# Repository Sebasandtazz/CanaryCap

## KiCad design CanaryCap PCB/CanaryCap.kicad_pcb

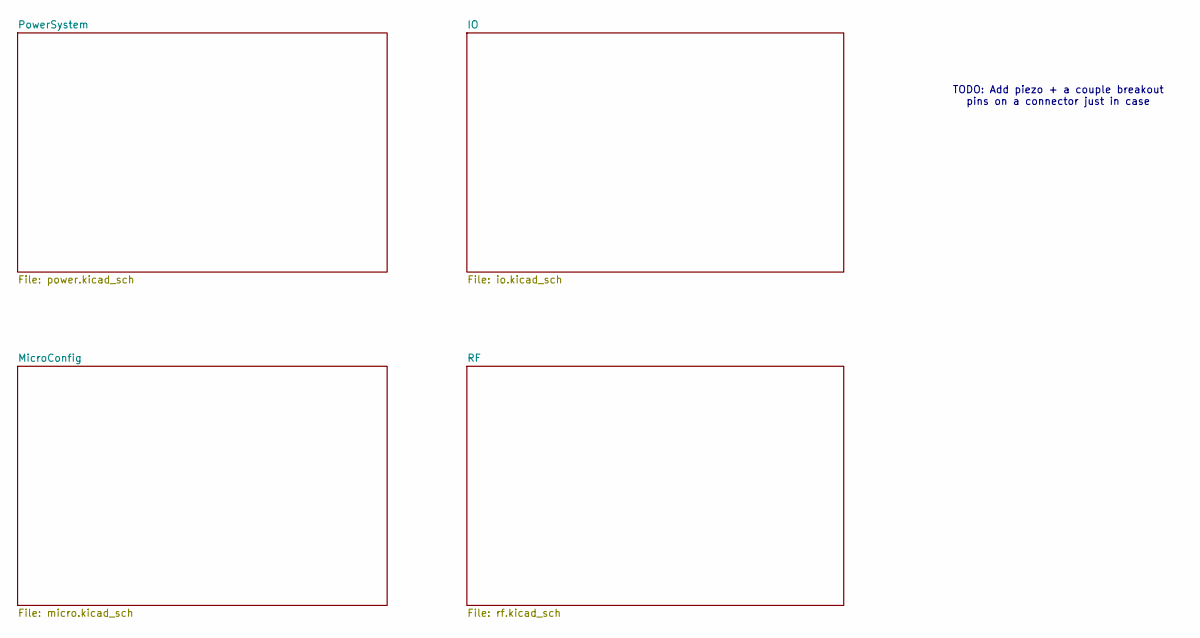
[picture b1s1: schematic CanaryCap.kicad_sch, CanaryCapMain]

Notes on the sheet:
TODO: Add piezo + a couple breakout pins on a connector just in case

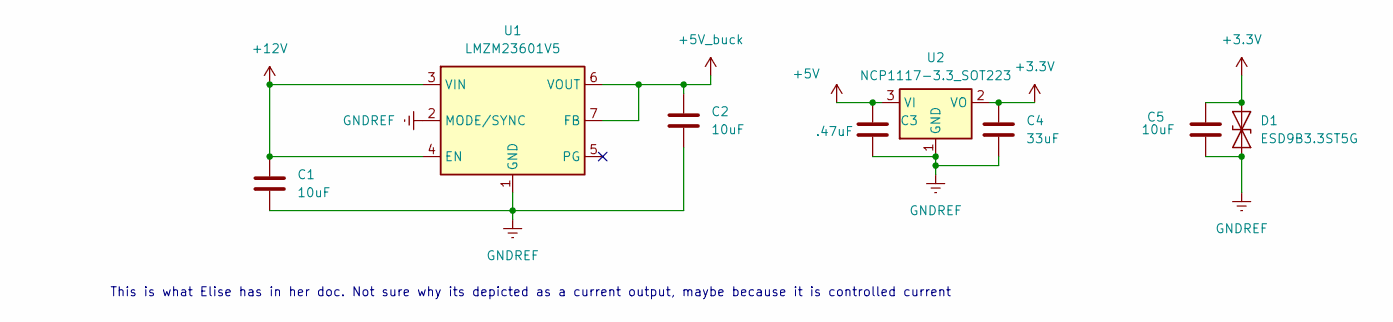
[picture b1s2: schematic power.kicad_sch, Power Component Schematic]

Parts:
C1, C2, C5: 10uF; C_0603_1608Metric_Pad1.08x0.95mm_HandSolder
C3: .47uF; C_0603_1608Metric_Pad1.08x0.95mm_HandSolder
C4: 33uF; C_0603_1608Metric_Pad1.08x0.95mm_HandSolder
D1: ESD9B3.3ST5G; D_SOD-923
U1: LMZM23601V5; Texas_SIL0010A_MicroSiP-10-1EP_3.8x3mm_P0.6mm_EP0.7x2.9mm_T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
U2: NCP1117-3.3_SOT223; SOT-223-3_TabPin2

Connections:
+3.3V: C4.1, C5.1, D1.2 (A2), U2.2 (VO); also elsewhere on the board
+5V: C3.1, U2.3 (VI); also elsewhere on the board
+5V_buck: C2.1, U1.6 (VOUT), U1.7 (FB); also elsewhere on the board
+12V: C1.1, U1.3 (VIN), U1.4 (EN); also elsewhere on the board
GNDREF: C1.2, C2.2, C3.2, C4.2, C5.2, D1.1 (A1), U1.1 (GND), U1.2 (MODE/SYNC), U1.11 (GND), U2.1 (GND); also elsewhere on the board

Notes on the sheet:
This is what Elise has in her doc. Not sure why its depicted as a current output, maybe because it is controlled current

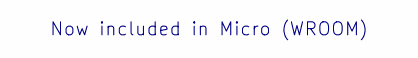
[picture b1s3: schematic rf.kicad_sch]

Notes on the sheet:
Now included in Micro (WROOM)

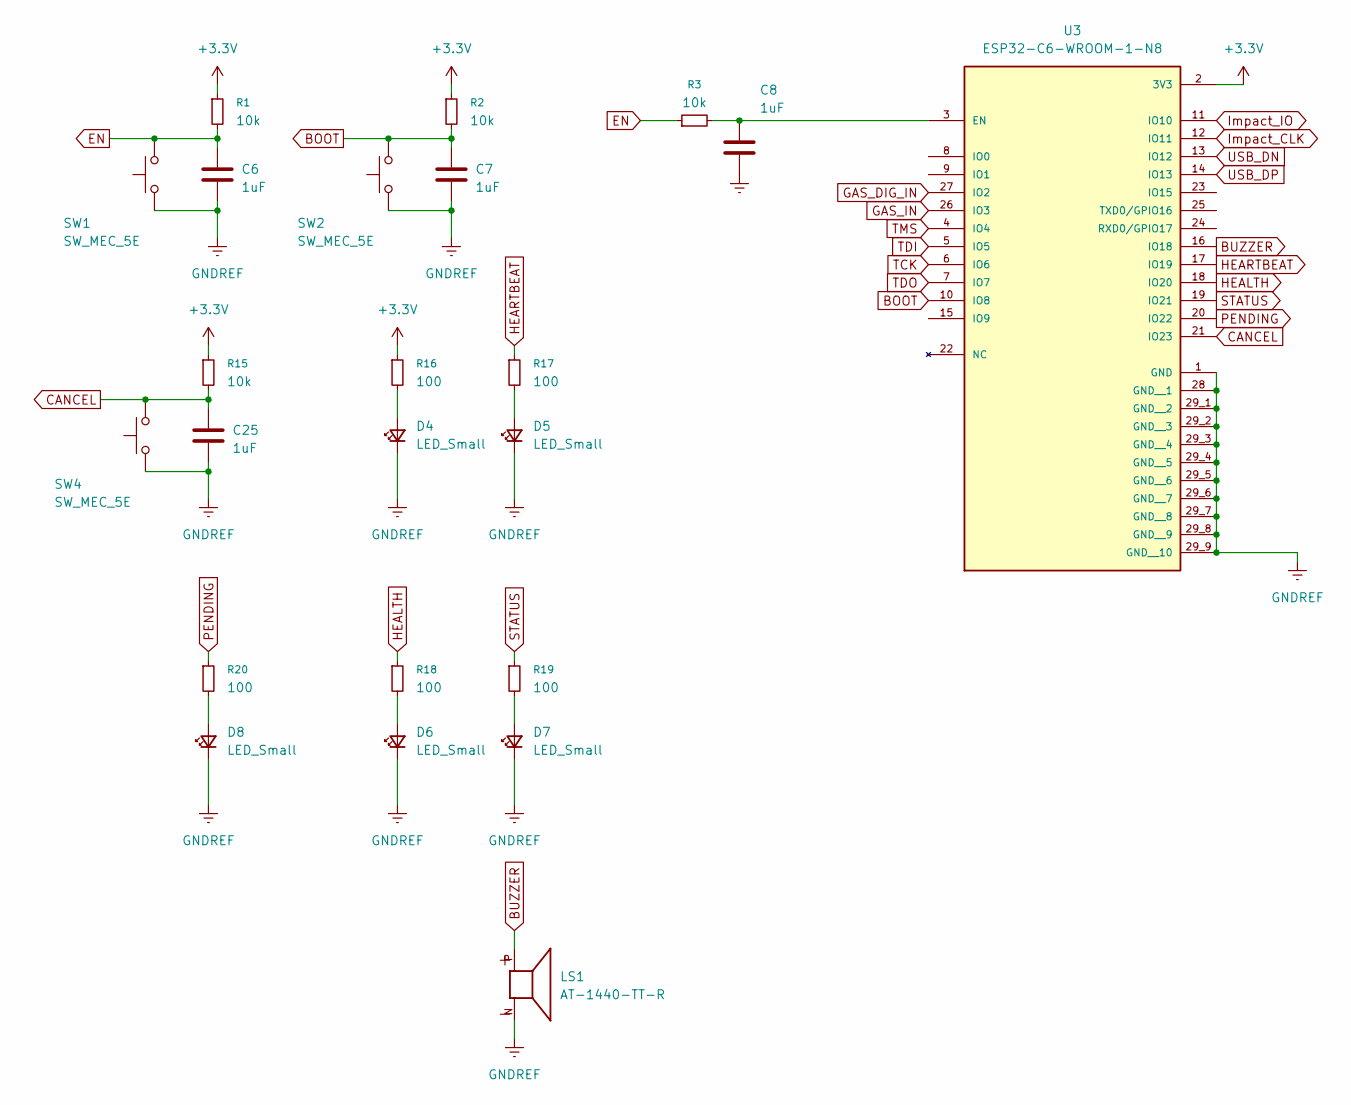
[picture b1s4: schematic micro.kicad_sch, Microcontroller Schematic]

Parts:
C6, C7, C8, C25: 1uF; C_0603_1608Metric_Pad1.08x0.95mm_HandSolder
D4, D5, D6, D7, D8: LED_Small; LED_0603_1608Metric_Pad1.05x0.95mm_HandSolder
LS1: AT-1440-TT-R; XDCR_AT-1440-TT-R; PARTREV 2014/07/25
R1, R2, R3, R15: 10k; R_0603_1608Metric_Pad0.98x0.95mm_HandSolder
R16, R17, R18, R19, R20: 100; R_0603_1608Metric_Pad0.98x0.95mm_HandSolder
SW1, SW2, SW4: SW_MEC_5E; SW_SPST_EVQP2_MiddlePushTravel_H2.5mm
U3: ESP32-C6-WROOM-1-N8; XCVR_ESP32-C6-WROOM-1-N8; PARTREV 1.0

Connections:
+3.3V: R1.1, R2.1, R15.1, R16.1, U3.2 (3V3); also elsewhere on the board
BOOT: C7.1, R2.2, SW2.2, U3.10 (IO8)
BUZZER: LS1.P, U3.16 (IO18)
CANCEL: C25.1, R15.2, SW4.2, U3.21 (IO23)
EN: C6.1, R1.2, R3.1, SW1.2
GAS_DIG_IN: U3.27 (IO2); also elsewhere on the board
GAS_IN: U3.26 (IO3); also elsewhere on the board
GNDREF: C6.2, C7.2, C8.2, C25.2, D4.1 (K), D5.1 (K), D6.1 (K), D7.1 (K), D8.1 (K), LS1.N, SW1.1, SW2.1, SW4.1, U3.1 (GND), U3.28 (GND__1), U3.29_1 (GND__2), U3.29_2 (GND__3), U3.29_3 (GND__4), U3.29_4 (GND__5), U3.29_5 (GND__6), U3.29_6 (GND__7), U3.29_7 (GND__8), U3.29_8 (GND__9), U3.29_9 (GND__10), U3.30_1, U3.30_2, U3.30_3, U3.30_4, U3.30_5, U3.30_6, U3.30_7, U3.30_8, U3.30_9, U3.30_10, U3.30_11, U3.30_12; also elsewhere on the board
HEALTH: R18.1, U3.18 (IO20); also elsewhere on the board
HEARTBEAT: R17.1, U3.17 (IO19); also elsewhere on the board
Impact_CLK: U3.12 (IO11); also elsewhere on the board
Impact_IO: U3.11 (IO10); also elsewhere on the board
unnamed: D4.2 (A), R16.2
unnamed: D5.2 (A), R17.2
unnamed: D6.2 (A), R18.2
unnamed: D7.2 (A), R19.2
unnamed: D8.2 (A), R20.2
unnamed: C8.1, R3.2, U3.3 (EN)
PENDING: R20.1, U3.20 (IO22); also elsewhere on the board
STATUS: R19.1, U3.19 (IO21); also elsewhere on the board
TCK: U3.6 (IO6); also elsewhere on the board
TDI: U3.5 (IO5); also elsewhere on the board
TDO: U3.7 (IO7); also elsewhere on the board
TMS: U3.4 (IO4); also elsewhere on the board
USB_DN: U3.13 (IO12); also elsewhere on the board
USB_DP: U3.14 (IO13); also elsewhere on the board

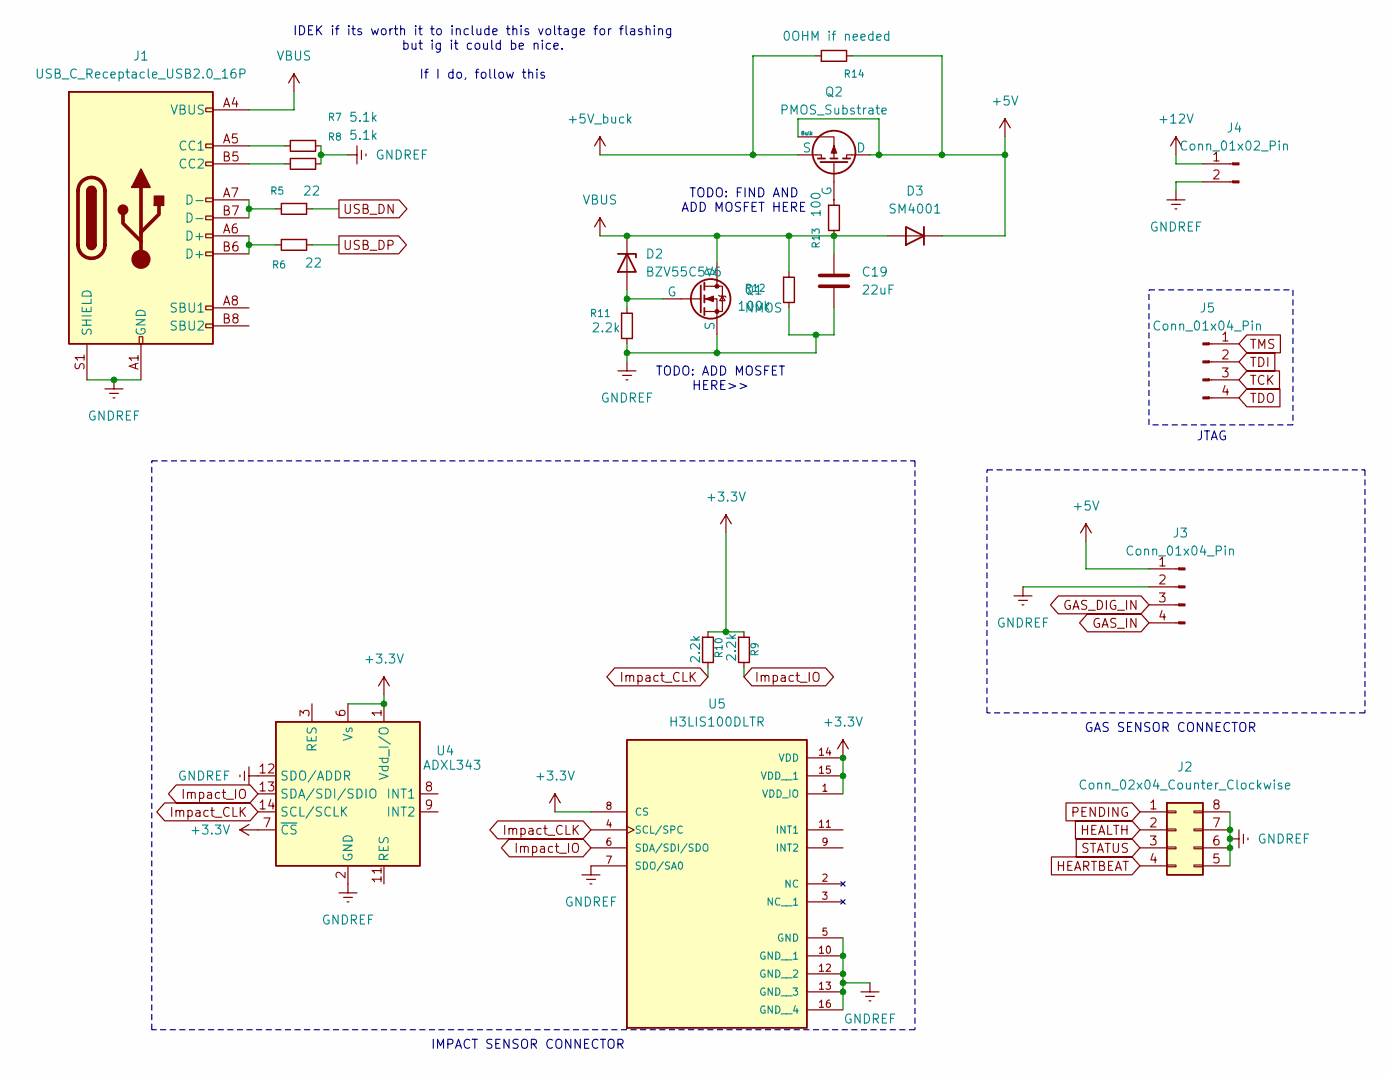
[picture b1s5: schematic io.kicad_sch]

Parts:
C19: 22uF; C_0603_1608Metric_Pad1.08x0.95mm_HandSolder
D2: BZV55C5V6; D_MiniMELF
D3: SM4001; D_MELF
J1: USB_C_Receptacle_USB2.0_16P; USB_C_Receptacle_G-Switch_GT-USB-7010ASV
J2: Conn_02x04_Counter_Clockwise; PinHeader_2x04_P2.54mm_Vertical
J3, J5: Conn_01x04_Pin; PinHeader_1x04_P2.54mm_Vertical
J4: Conn_01x02_Pin; PinHeader_1x02_P2.54mm_Vertical
Q1: NMOS; SOT-23
Q2: PMOS_Substrate; SOT-223
R5, R6: 22; R_0603_1608Metric_Pad0.98x0.95mm_HandSolder
R7, R8: 5.1k; R_0603_1608Metric_Pad0.98x0.95mm_HandSolder
R9, R10, R11: 2.2k; R_0603_1608Metric_Pad0.98x0.95mm_HandSolder
R12: 100k; R_0603_1608Metric_Pad0.98x0.95mm_HandSolder
R13: 100; R_0603_1608Metric_Pad0.98x0.95mm_HandSolder
R14: 0OHM if needed; R_0603_1608Metric_Pad0.98x0.95mm_HandSolder
U4: ADXL343; LGA-14_3x5mm_P0.8mm_LayoutBorder1x6y
U5: H3LIS100DLTR; PARTREV 2

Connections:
+3.3V: R9.1, R10.1, U4.1 (Vdd_I/O), U4.6 (Vs), U4.7 (~CS), U5.1 (VDD_IO), U5.8 (CS), U5.14 (VDD), U5.15 (VDD__1); also elsewhere on the board
+5V: D3.1 (K), J3.1, Q2.2 (D), Q2.4 (Bulk), R14.2; also elsewhere on the board
+5V_buck: Q2.3 (S), R14.1; also elsewhere on the board
+12V: J4.1; also elsewhere on the board
GAS_DIG_IN: J3.3; also elsewhere on the board
GAS_IN: J3.4; also elsewhere on the board
GNDREF: C19.2, J1.A1 (GND), J1.A12 (GND), J1.B1 (GND), J1.B12 (GND), J1.S1 (SHIELD), J2.5, J2.6, J2.7, J2.8, J3.2, J4.2, Q1.2 (S), R7.1, R8.1, R11.2, R12.2, U4.2 (GND), U4.4 (GND), U4.5 (GND), U4.12 (SDO/ADDR), U5.5 (GND), U5.7 (SDO/SA0), U5.10 (GND__1), U5.12 (GND__2), U5.13 (GND__3), U5.16 (GND__4); also elsewhere on the board
HEALTH: J2.2; also elsewhere on the board
HEARTBEAT: J2.4; also elsewhere on the board
Impact_CLK: R10.2, U4.14 (SCL/SCLK), U5.4 (SCL/SPC); also elsewhere on the board
Impact_IO: R9.2, U4.13 (SDA/SDI/SDIO), U5.6 (SDA/SDI/SDO); also elsewhere on the board
unnamed: D2.2 (A), Q1.1 (G), R11.1
unnamed: J1.A5 (CC1), R7.2
unnamed: J1.B5 (CC2), R8.2
unnamed: J1.A6 (D+), J1.B6 (D+), R6.2
unnamed: J1.A7 (D-), J1.B7 (D-), R5.2
unnamed: Q2.1 (G), R13.1
PENDING: J2.1; also elsewhere on the board
STATUS: J2.3; also elsewhere on the board
TCK: J5.3; also elsewhere on the board
TDI: J5.2; also elsewhere on the board
TDO: J5.4; also elsewhere on the board
TMS: J5.1; also elsewhere on the board
USB_DN: R5.1; also elsewhere on the board
USB_DP: R6.1; also elsewhere on the board
VBUS: C19.1, D2.1 (K), D3.2 (A), J1.A4 (VBUS), J1.A9 (VBUS), J1.B4 (VBUS), J1.B9 (VBUS), Q1.3 (D), R12.1, R13.2

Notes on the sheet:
TODO: FIND AND ADD MOSFET HERE
IDEK if its worth it to include this voltage for flashing but ig it could be nice. If I do, follow this
TODO: ADD MOSFET HERE>>
IMPACT SENSOR CONNECTOR
GAS SENSOR CONNECTOR
JTAG

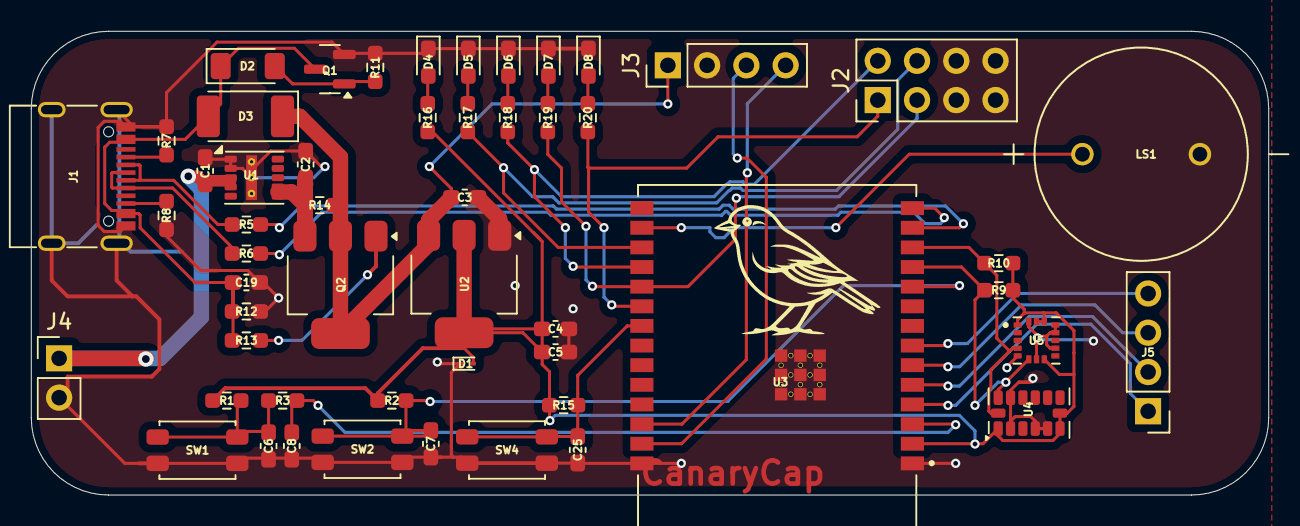
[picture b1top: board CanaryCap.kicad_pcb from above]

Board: 2 copper layers, 80.0 x 30.0 mm, 53 parts (0 on the bottom side), 36 nets.

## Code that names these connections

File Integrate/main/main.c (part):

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#define LED_GPIO1                   19 //CONFIG_LED_GPIO
#define LED_GPIO2                   20 //CONFIG_LED_GPIO

#define BUTTON_GPIO                 23  // Boot button for impact cancel and Zigbee reset
#define SPIFFS_CLEAR_BUTTON_GPIO    8   // Boot button for SPIFFS clear
#define BUZZER_GPIO                 18 //CONFIG_BUZZER_GPIO
#define HEARTBEAT_LED_GPIO          19 //CONFIG_HEARTBEAT_LED_GPIO
#define HEALTH_LED_GPIO            20 //CONFIG_HEALTHY_LED_GPIO
#define STATUS_LED_GPIO            21 //CONFIG_STATUS_LED_GPIO
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//Def for Buzzer
#define LEDC_TIMER              LEDC_TIMER_0
#define LEDC_MODE               LEDC_LOW_SPEED_MODE
#define LEDC_OUTPUT_IO          (18) // Buzzer GPIO (matches BUZZER_GPIO)
#define LEDC_CHANNEL            LEDC_CHANNEL_0
#define LEDC_DUTY_RES           LEDC_TIMER_13_BIT // Set duty resolution to 13 bits
#define LEDC_DUTY               (4096) // Set duty to 50%. (2 ** 13) * 50% = 4096
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        /* Local alerts for severe impacts - cancellable with button */
        if (severity == CANARY_IMPACT_SEVERE) {
            severe_alert_active = true;
            ESP_LOGW(TAGZB, "LOCAL SEVERE IMPACT - Press GPIO23 button within 10s to cancel");
            
            /* Allocate impact data to pass to task */
            typedef struct {
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        /* Alternate between STATUS and HEALTH LEDs with continuous buzzer */
        if (status_led_on) {
            gpio_set_level(STATUS_LED_GPIO, 0);   // STATUS ON
            gpio_set_level(HEALTH_LED_GPIO, 1);   // HEALTH OFF
        } else {
            gpio_set_level(STATUS_LED_GPIO, 1);   // STATUS OFF
            gpio_set_level(HEALTH_LED_GPIO, 0);   // HEALTH ON
        }
        status_led_on = !status_led_on;  // Toggle for next iteration
        
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{
    ESP_LOGE(TAGZB, "NETWORK DISCONNECTED/DEVICE LEFT - Flashing PENDING+HEALTH+STATUS until reconnection");
    while (network_disconnected_alert_active) {
        /* Flash PENDING, HEALTH, and STATUS LEDs with constant buzzer */
        gpio_set_level(HEALTH_LED_GPIO, 0);     // ON
        gpio_set_level(STATUS_LED_GPIO, 0);     // ON
        gpio_set_level(PENDING_LED_GPIO, 0);    // ON
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    } else {
        ESP_LOGE(TAGZB, "*** DEVICE LEFT NETWORK: 0x%04x ***", device_addr);
        
        /* Activate continuous device leave alert - flash PENDING+HEALTH+STATUS with constant buzzer */
        network_disconnected_alert_active = true;
        xTaskCreate(network_disconnect_alert_task, "device_leave_alert", 2048, NULL, 7, NULL);
    }
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    ESP_LOGI(TAGZB, "Allocated LEDs initialized: HEARTBEAT=%d, HEALTH=%d, STATUS=%d, PENDING=%d",
             HEARTBEAT_LED_GPIO, HEALTH_LED_GPIO, STATUS_LED_GPIO, PENDING_LED_GPIO);

    // Configure GPIO 23 button input (severe alert cancel & factory reset)
    gpio_config_t io_conf = {
        .pin_bit_mask = 1ULL << BUTTON_GPIO,
        .mode = GPIO_MODE_INPUT,
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
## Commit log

2025-08-29 Initial Commit of board files for team share
2025-08-29 Update LICENSE
2025-08-29 Reorg structure
2025-09-18 Put very basic symbols which we plan to use into the schematics, nothing else :(
2025-09-19 Started some basic board definition and component selection DO NOT USE LAYOUT
2025-09-19 Deleted duplicate files
2025-09-22 create main.c file empty for now
2025-09-30 not sure what this is tbh
2025-09-30 Sebastians Nightmare
2025-09-30 We gotta figure out git ignore
2025-09-30 GIT IGNORE ALL
2025-09-30 Pushing for new MCU
2025-09-30 no blink
2025-10-02 Board progress
2025-10-02 Done with ts for the night
2025-10-02 Bruh
2025-10-06 Updated schematics for justin to work
2025-10-07 new changes
2025-10-07 lets see if this works?
2025-10-07 HELP ME
2025-10-07 PCB layout started
2025-10-07 Deleted windows blink
2025-10-08 Added todo
2025-10-09 cmake
2025-10-09 we tried..
2025-10-09 FIXED IT MF
2025-10-10 Laid out more
2025-10-13 Finished level for packaging
2025-10-14 changed main
2025-10-14 another change
2025-10-14 added examples to meet my specs - Justin
2025-10-15 comment
2025-10-21 bruh bruh bruh
2025-10-21 Added my files
2025-10-23 Me phinks I did it
2025-10-23 YIPPEE
2025-10-30 my stuff - justin
    Git Ignore - sebastian
2025-11-04 git ignore
2025-11-06 -integrated accel
2025-11-06 opened it
2025-11-13 yuh for vinnie
2025-11-18 All individual tasks work (i2c, adc, and zigbee)
    when in doubt, restore.
2025-11-20 Cleaning up unnecessary folders
2025-11-20 Capcb updates
2025-11-25 Working Zigbee
    I got the zigbee to work with the devkits
2025-12-02 clean up
2025-12-02 works on pcb
    sebastian dont touch it
2025-12-02 fullcleaned
2025-12-03 fixed?
2025-12-04 It works
    There is beeping, signals cancel and messages are across zigbee. Its presentable.
2025-12-08 so far it works by communicating to all devices, but need gas tuning and network lost tuning
2025-12-09 detects network left
2025-12-11 War is over, we can go home now
2025-12-11 demo day
